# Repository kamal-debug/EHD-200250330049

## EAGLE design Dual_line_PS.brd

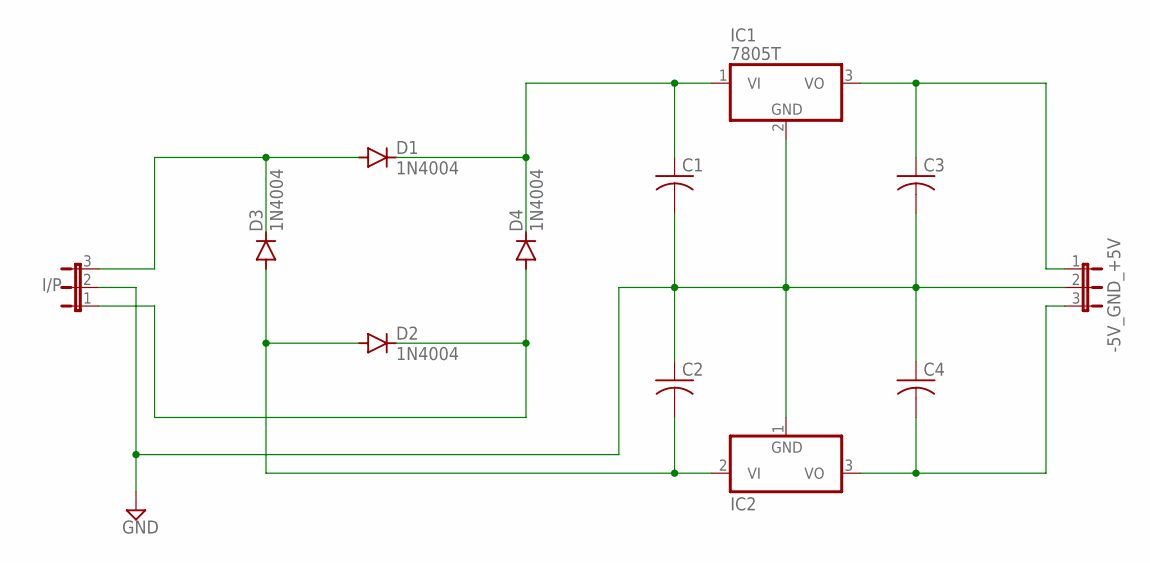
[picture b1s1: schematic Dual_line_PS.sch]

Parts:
-5V_GND_+5V: JP2E; JP2
C1, C2, C3, C4: C-US025-024X044; C025-024X044
D1, D2, D3, D4: 1N4004; DO41-10
I/P: JP2E; JP2
IC1: 7805T; TO220H
IC2: 7905T; TO220H

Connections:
GND: -5V_GND_+5V.2, C1.2, C2.1, C3.2, C4.1, I/P.2, IC1.2 (GND), IC2.1 (GND)
unnamed: D1.A, D3.C, I/P.3
unnamed: D2.C, D4.A, I/P.1
unnamed: C2.2, D2.A, D3.A, IC2.2 (VI)
unnamed: C1.1, D1.C, D4.C, IC1.1 (VI)
unnamed: -5V_GND_+5V.3, C4.2, IC2.3 (VO)
unnamed: -5V_GND_+5V.1, C3.1, IC1.3 (VO)

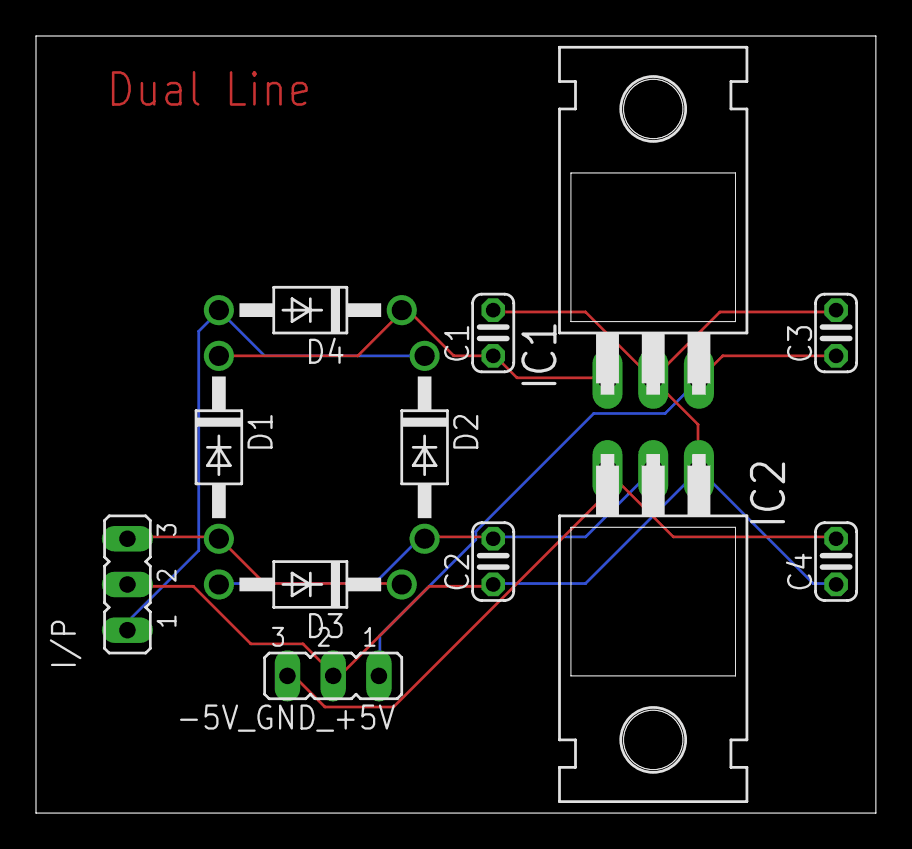
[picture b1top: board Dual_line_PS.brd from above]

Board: 2 copper layers, 46.7 x 43.2 mm, 12 parts (0 on the bottom side), 7 nets.

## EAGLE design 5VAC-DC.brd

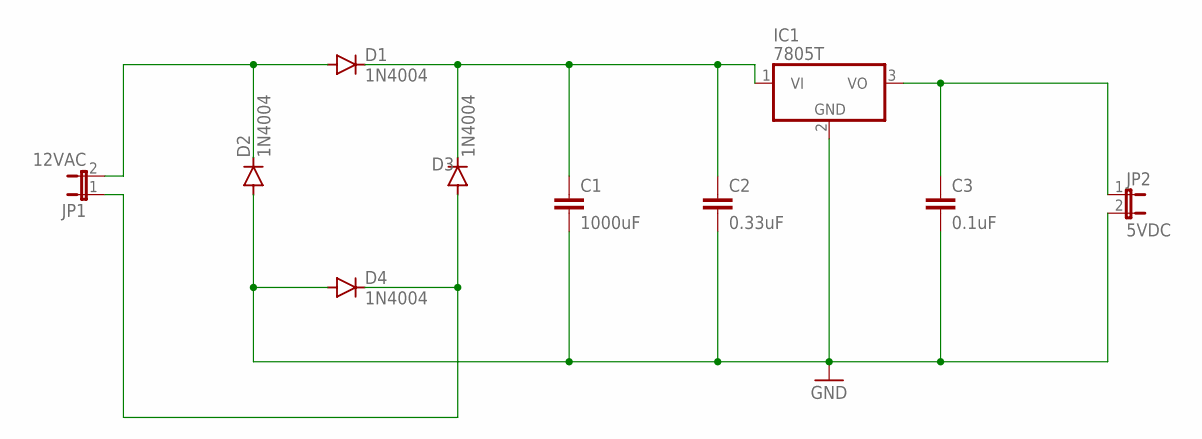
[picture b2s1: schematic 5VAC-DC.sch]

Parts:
C1: 1000uF; C2.5-3
C2: 0.33uF; C2.5-3
C3: 0.1uF; C2.5-3
D1, D2, D3, D4: 1N4004; DO41-10
IC1: 7805T; TO220H
JP1: 12VAC; JP1
JP2: 5VDC; JP1

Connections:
GND: C1.2, C2.2, C3.2, D2.A, D4.A, IC1.2 (GND), JP2.2
unnamed: D1.A, D2.C, JP1.2
unnamed: C1.1, C2.1, D1.C, D3.C, IC1.1 (VI)
unnamed: D3.A, D4.C, JP1.1
unnamed: C3.1, IC1.3 (VO), JP2.1

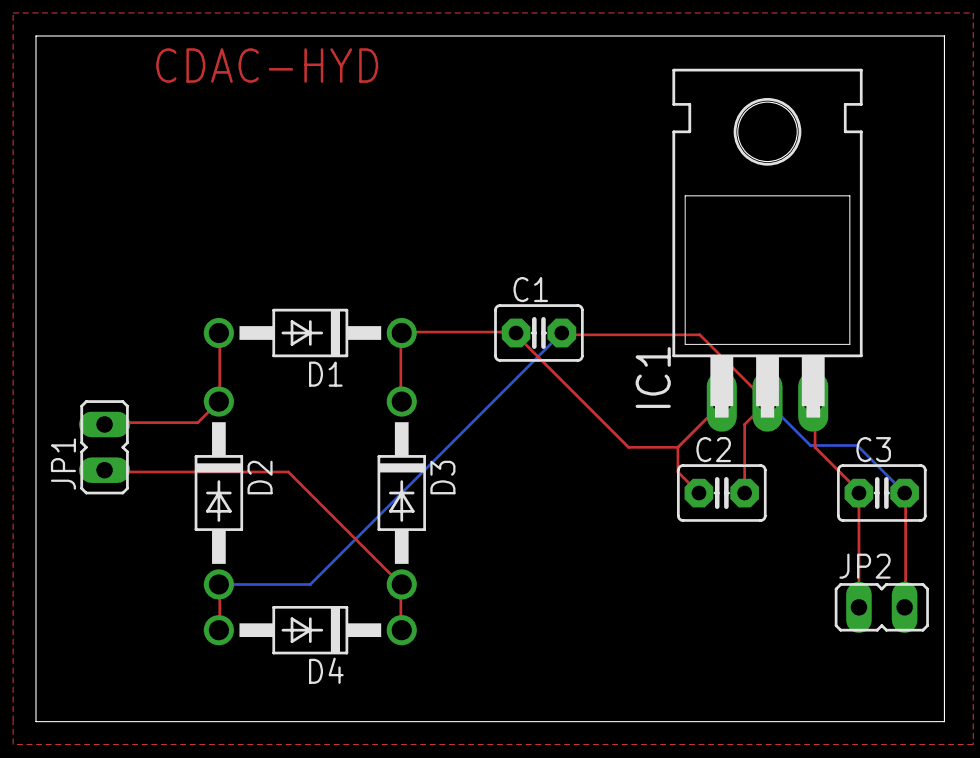
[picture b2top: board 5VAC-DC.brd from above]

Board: 2 copper layers, 50.5 x 38.1 mm, 10 parts (0 on the bottom side), 5 nets.
